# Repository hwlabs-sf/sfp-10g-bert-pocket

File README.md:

# sfp-10g-bert-pocket

A 10.3125 Gbit/s SFP+ bit-error-rate tester and optical power monitor, small enough
to be a pocket board: a 64-bit parallel PRBS-31 generator and checker in Verilog,
an SFF-8472 I2C poller, a four-layer SFP+ carrier, and a host CLI that turns raw
diagnostic bytes into degrees, volts, milliamps and dBm.

It is a reference design, not a product. Everything in it is either a published
standard or arithmetic you can re-derive: IEEE 802.3ae clause 49 for the pattern
and the line rate, SFF-8472 rev 12.4 for the diagnostic registers. No vendor IP,
no encrypted blocks, no "contact us for the core".

---

## What the numbers are

| Quantity | Value | Where it comes from |
| :--- | :--- | :--- |
| Line rate | 10.3125 Gbit/s | 10GBASE-R, 64b/66b coded |
| Clock | 161.1328125 MHz | 10.3125 G / 64 |
| Pattern | PRBS-31, G(x) = x^31 + x^28 + 1 | IEEE 802.3ae 49.2.8 |
| Checker | self-synchronising, 31-bit window | predicts s[n] from s[n-28] ^ s[n-31] |
| DDM | SFF-8472 A2h, bytes 0x60..0x69 | 1/256 °C, 100 µV, 2 µA, 0.1 µW |
| BER, 100 s, zero errors | < 2.91e-12 (95 %) | −ln(0.05) / 1.031e12 bits |

At 10.3125 Gbit/s a 100-second run pushes 1.031e12 bits through the link. If the
counter sees nothing, the honest statement is not "BER = 0" but "BER is below
2.91e-12 at 95 % confidence", which is what `host/bert_cli.py ber` prints.

## Layout

```
rtl/prbs31_64b.v        64-bit parallel generator + self-sync checker
rtl/ber_counter.v       saturating bit/error counters, latch-on-read snapshot
rtl/sff8472_ddm_i2c.v   I2C master polling A2h 0x60..0x69
rtl/tb_prbs31.v         self-checking testbench, serial golden model inside
rtl/tb_sff8472_i2c.v    bus-level testbench with an A2h slave model
hardware/sfp_bert.kicad_sch / .kicad_pcb / BOM.csv
host/bert_cli.py        DDM decode, BER + Poisson bound, offline demo
tests/test_bert_and_dfm.py
architecture.svg
```

## The generator is written out, not looped

A bit-serial PRBS-31 is nine lines of Verilog. This one is unrolled 64 clocks
deep, because the parallel form is where the mistakes live: a single wrong tap in
one of the 64 rows still produces a plausible-looking stream, and you only find
out when a link fails BER at 1e-9 for no visible reason.

So each row is written as the XOR of the state bits that feed it:

```verilog
assign tx_bits[ 0] = state[30];
assign tx_bits[ 1] = state[29];
...
assign tx_bits[31] = state[27] ^ state[30];
```

and `tests/test_bert_and_dfm.py` parses all 95 rows straight out of the Verilog
source, evaluates them, and compares 10 048 bits against a bit-serial LFSR written
independently in Python, on two different seeds. If someone edits a row, the test
fails on the first bit that disagrees.

The checker is the textbook self-synchronising form: it predicts each received bit
from the two bits 28 and 31 positions earlier *in the received stream*. That means
no frame boundary and no handshake -- it locks after 31 bits and re-locks 31 bits
after a phase slip. It also means one corrupted bit is reported as three errors
(itself plus the two predictions that read it), which is a property of the
circuit, not a defect, and the testbench asserts exactly that.

## Hardware

A 60 × 40 mm four-layer carrier:

- **F.Cu / B.Cu** signal, **In1.Cu** solid ground, **In2.Cu** 3V3.
- TD and RD pairs are 0.15 mm wide with a 0.15 mm gap, referenced to In1 through
  100 µm of prepreg, which lands close to 100 Ω differential without a field
  solver. The stack-up callout is in `architecture.svg`.
- 100 nF 0201 AC coupling on all four lines, ground void under the pads.
- TPS7A9401 (4.4 µVrms) for the module rail, not a generic buck: SFP+ receivers
  care about rail noise more than they care about efficiency.
- CP2102N bridges I2C to USB so a laptop can poll the DDM without an FPGA.
- 161.1328125 MHz LVDS oscillator for boards that need to supply the reference
  clock instead of receiving it.

`hardware/BOM.csv` carries the primary part and an alternate for every line, with
the LCSC column filled where the code was verified and `tbd` where purchasing has
to confirm it at order time -- a BOM that pretends to know every distributor code
is a BOM that has never been ordered.

The board passes `kicad-dfm-precheck` with zero findings: 13 vias, 24 through-hole
pads, no annular ring under 0.15 mm, no placeholder values, no pad left on an
`unconnected-*` net.

## Running it

```bash
# everything that does not need a simulator
python -m unittest discover -s tests -v

# both testbenches, if iverilog is installed
iverilog -g2005 -o tb.vvp rtl/prbs31_64b.v rtl/ber_counter.v rtl/tb_prbs31.v && vvp tb.vvp
iverilog -g2005 -o i2c.vvp rtl/sff8472_ddm_i2c.v rtl/tb_sff8472_i2c.v && vvp i2c.vvp

# the host side
python host/bert_cli.py demo
python host/bert_cli.py ddm --hex 1a4080e800c803e800fa
python host/bert_cli.py ber --errors 0 --seconds 100
```

The DFM test looks for `kicad-dfm-precheck` next to this repository and skips
with a message if it is not there, rather than passing quietly.

## What is not here

No vendor-specific primitives, no SERDES transceiver wrapper (that is the FPGA
vendor's IP and it is not portable), no firmware for a specific USB bridge, and no
claim that this has been run against a live module -- the I2C master is verified
against a bus-level model, not against silicon. Those gaps are stated because a
reference design that hides its edges is worse than no reference design.

MIT licensed. Built and tested on a bench in Shenzhen.

[hengwu.online/labs](https://hengwu.online/labs/) · [hello@hengwu.online](mailto:hello@hengwu.online)

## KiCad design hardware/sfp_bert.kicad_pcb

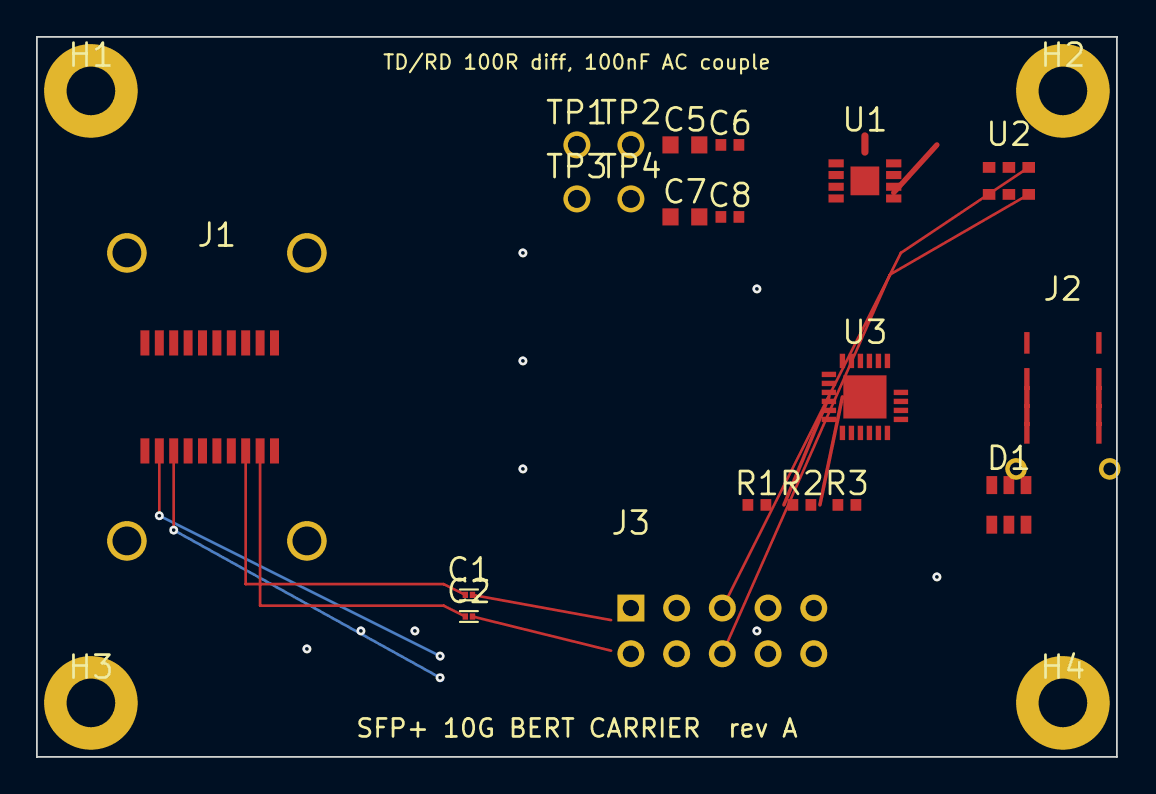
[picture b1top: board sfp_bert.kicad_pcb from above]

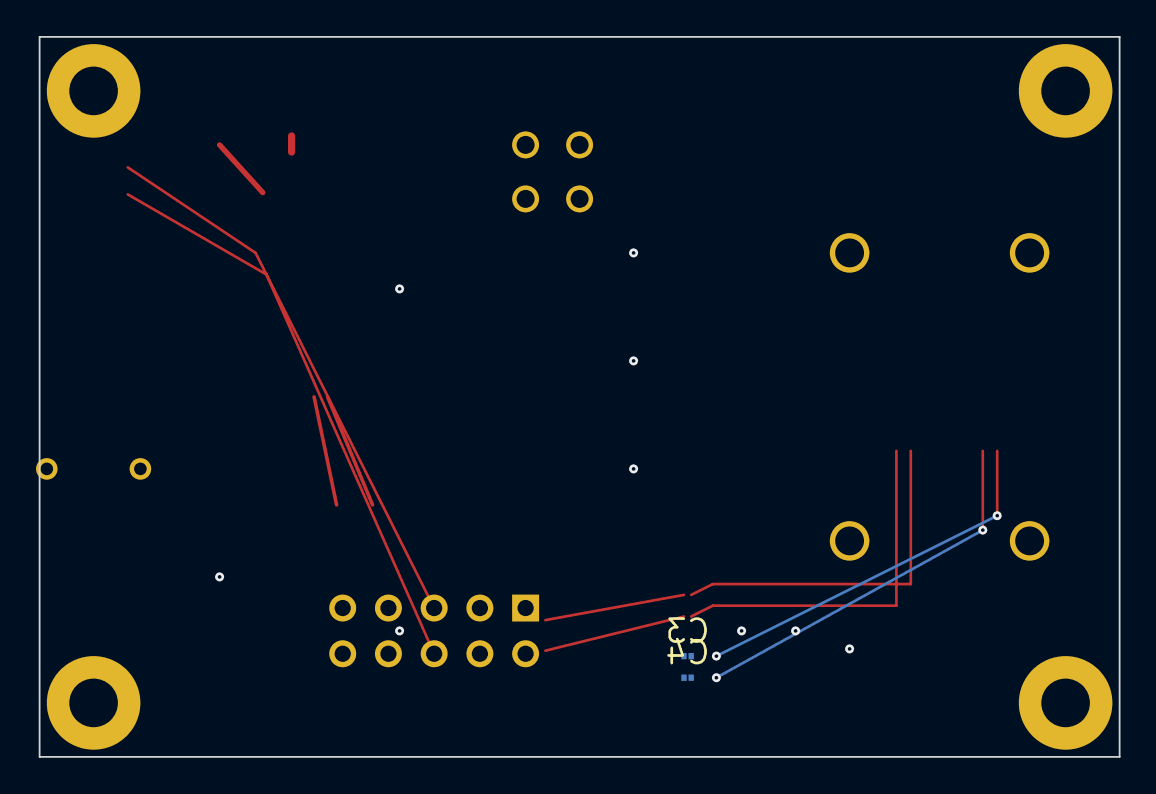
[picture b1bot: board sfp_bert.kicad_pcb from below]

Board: 4 copper layers, 60.0 x 40.0 mm, 26 parts (2 on the bottom side), 19 nets.

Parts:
C1, C2, C3, C4: 100nF; C_0201_0603Metric
C5: 10uF; C_0603_1608Metric
C6: 1uF; C_0402_1005Metric
C7: 4.7uF; C_0603_1608Metric
C8: 100nF; C_0402_1005Metric
D1: USBLC6-2SC6; SOT-23-6
H1, H2, H3, H4: MountingHole_2.7mm; MountingHole_2.7mm_Pad
J1: SFP+_Cage_20P
J2: USB_C_Receptacle; USB_C_Receptacle_HRO_TYPE-C-31-M-12
J3: TD/RD/REFCLK; PinHeader_2x05_P2.54mm_Vertical
R1, R2: 4.7k; R_0402_1005Metric
R3: 10k; R_0402_1005Metric
TP1: TD_LOOP; TestPoint_Pad_D1.5mm
TP2: RD_LOOP; TestPoint_Pad_D1.5mm
TP3: SDA; TestPoint_Pad_D1.5mm
TP4: SCL; TestPoint_Pad_D1.5mm
U1: TPS7A9401; VSON-8-1EP_3x3mm_P0.65mm
U2: 161.1328125MHz; Oscillator_SMD_Si545_3.2x2.5mm
U3: CP2102N-A02-GQFN24; QFN-24-1EP_4x4mm_P0.5mm

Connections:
+3V3: C5.1, C6.1, R1.1, R2.1, U1.2, U1.4, U2.1, U3.6, U3.9, U3.11, U3.12, U3.13, U3.14, U3.15, U3.17, U3.18, U3.19, U3.20, U3.21, U3.22
+3V3_SFP: C7.1, C8.1, J1.9, J1.15, J1.16, J3.7, R3.1, U1.6, U1.7
GND: C5.2, C6.2, C7.2, C8.2, D1.2, H1.1, H2.1, H3.1, H4.1, J1.1, J1.7, J1.10, J1.11, J1.14, J1.17, J1.20, J2.A5, J2.B5, J2.S1, J2.S2, J3.8, U1.3, U1.8, U1.9, U2.2, U2.5, U2.6, U3.4, U3.10, U3.16, U3.23
RD+: C3.1, J1.13
RD+_C: C3.2, J3.3, TP2.1
RD-: C4.1, J1.12
RD-_C: C4.2, J3.4
REFCLK+: J3.5, U2.3
REFCLK-: J3.6, U2.4
SCL: J1.5, J3.10, R2.2, TP4.1, U3.8
SDA: J1.4, J3.9, R1.2, TP3.1, U3.7
TD+: C1.1, J1.18
TD+_C: C1.2, J3.1, TP1.1
TD-: C2.1, J1.19
TD-_C: C2.2, J3.2
TX_DISABLE: J1.3, R3.2
USB_DM: D1.3, D1.6, J2.A7, J2.B7, U3.1
USB_DP: D1.1, D1.4, J2.A6, J2.B6, U3.2
VBUS: D1.5, J2.A1, J2.A4, J2.B1, J2.B4, U1.1, U3.3, U3.5
